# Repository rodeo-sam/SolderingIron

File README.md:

SolderingIron
=============

Idea for an OpenSource Soldering Iron

This project is just another avr based soldering iron. Since professional equipment is quite pricy and not very complicated this projects takes a good, changeable soldering iron tip like the Weller RT1 and provides all the electronics behind that.

## Features
* open hardware (schematic and layout made in Eagle 7.2 freeware license)
* open firmware written in C (not ready to use right now)
* fast heatup
* saving and restoring temperature to and from EEPROM
* high-precision op-amp for temperature measurement
* safety measures against overheating and controller crashes
* automatic temperature control (pid controller)
* different temperature scales available (recompiling necessary)
* solder tip rest detection via hall sensor (optional)
* almost all parts are available from the [Seeedstudio Open Parts Library](http://www.seeedstudio.com/wiki/Open_parts_library)

## How does it work
* 5V for logic
* 12V for soldering iron
* ATmega328p controlled

### Temperature measure
The thermo-voltage signal is amplified by an op-amp with a gain
	`g = 1 + R1/R2 = 1 + 51k/100 = 511`
this signal is converted by ADC0 using Vcc=5V as voltage reference

### Solder tip detection
Solved by a hall sensor connected to ADC2. This sensor is powered by 5V

## References
### Links:
* [arduino uno shield](http://www.martin-kumm.de/wiki/doku.php?id=Projects:SMD_Solderstation)
  * Forum discussion + group order coordination [Thema: DIY SMD - Lötstation Ersatz für (WELLER)](http://fpv-community.de/showthread.php?41335-DIY-SMD-Lötstation-Ersatz-für-(WELLER))
* [original Weller cable](http://www.pewa.de/cgi-bin/cosmoshop/lshop.cgi?action=showdetail&wkid=1415179514-14110&ls=d&nc=1415179711-29852&rubnum=&artnum=C-51042699&file=&gesamt_zeilen=0Tsuche--silikon)
* unfinished project [Custom Weller WSM 1 style controller for RT series tips](http://dangerousprototypes.com/forum/viewtopic.php?f=19&t=3583)
* [Thermoelement im Weller WMRP.](http://www.mikrocontroller.net/topic/175412#1686071)

### Datasheets:
* power MOSFET [IRF7424](http://www.irf.com/product-info/datasheets/data/irf7424.pdf)
* Voltage regulator [REG1117](http://www.ti.com/lit/pdf/SBVS001)
* uC [ATmega328P](http://www.atmel.com/devices/atmega328p.aspx)
* Quad OP-Amp [LM324D](http://pdf1.alldatasheet.com/datasheet-pdf/view/22759/STMICROELECTRONICS/LM324D.html)
* Single OP-Amp [OPA336u](http://www.ti.com/lit/ds/symlink/opa336.pdf)
* Solder Tip [Weller RT1](http://datasheet.octopart.com/RT1-Cooper-Tools-datasheet-13539183.pdf)
* Solder Tip detector [Hallsensor unipolar](http://www.reichelt.de/index.html?&ACTION=7&LA=3&OPEN=0&INDEX=0&FILENAME=B400%252FTLE4905L_TLE4935L_TLE4945L_TLE4935-2L%2523SIE.pdf)

### Current State:
* hardware version 1.2 is almost ready to be produced
* optimized bill of materials by reducing unnecessary components
* PCB measures 5cm x 5cm
* individual 7-segment displays in use (broader availability)
* I2C is now unused and can be used for additional hardware

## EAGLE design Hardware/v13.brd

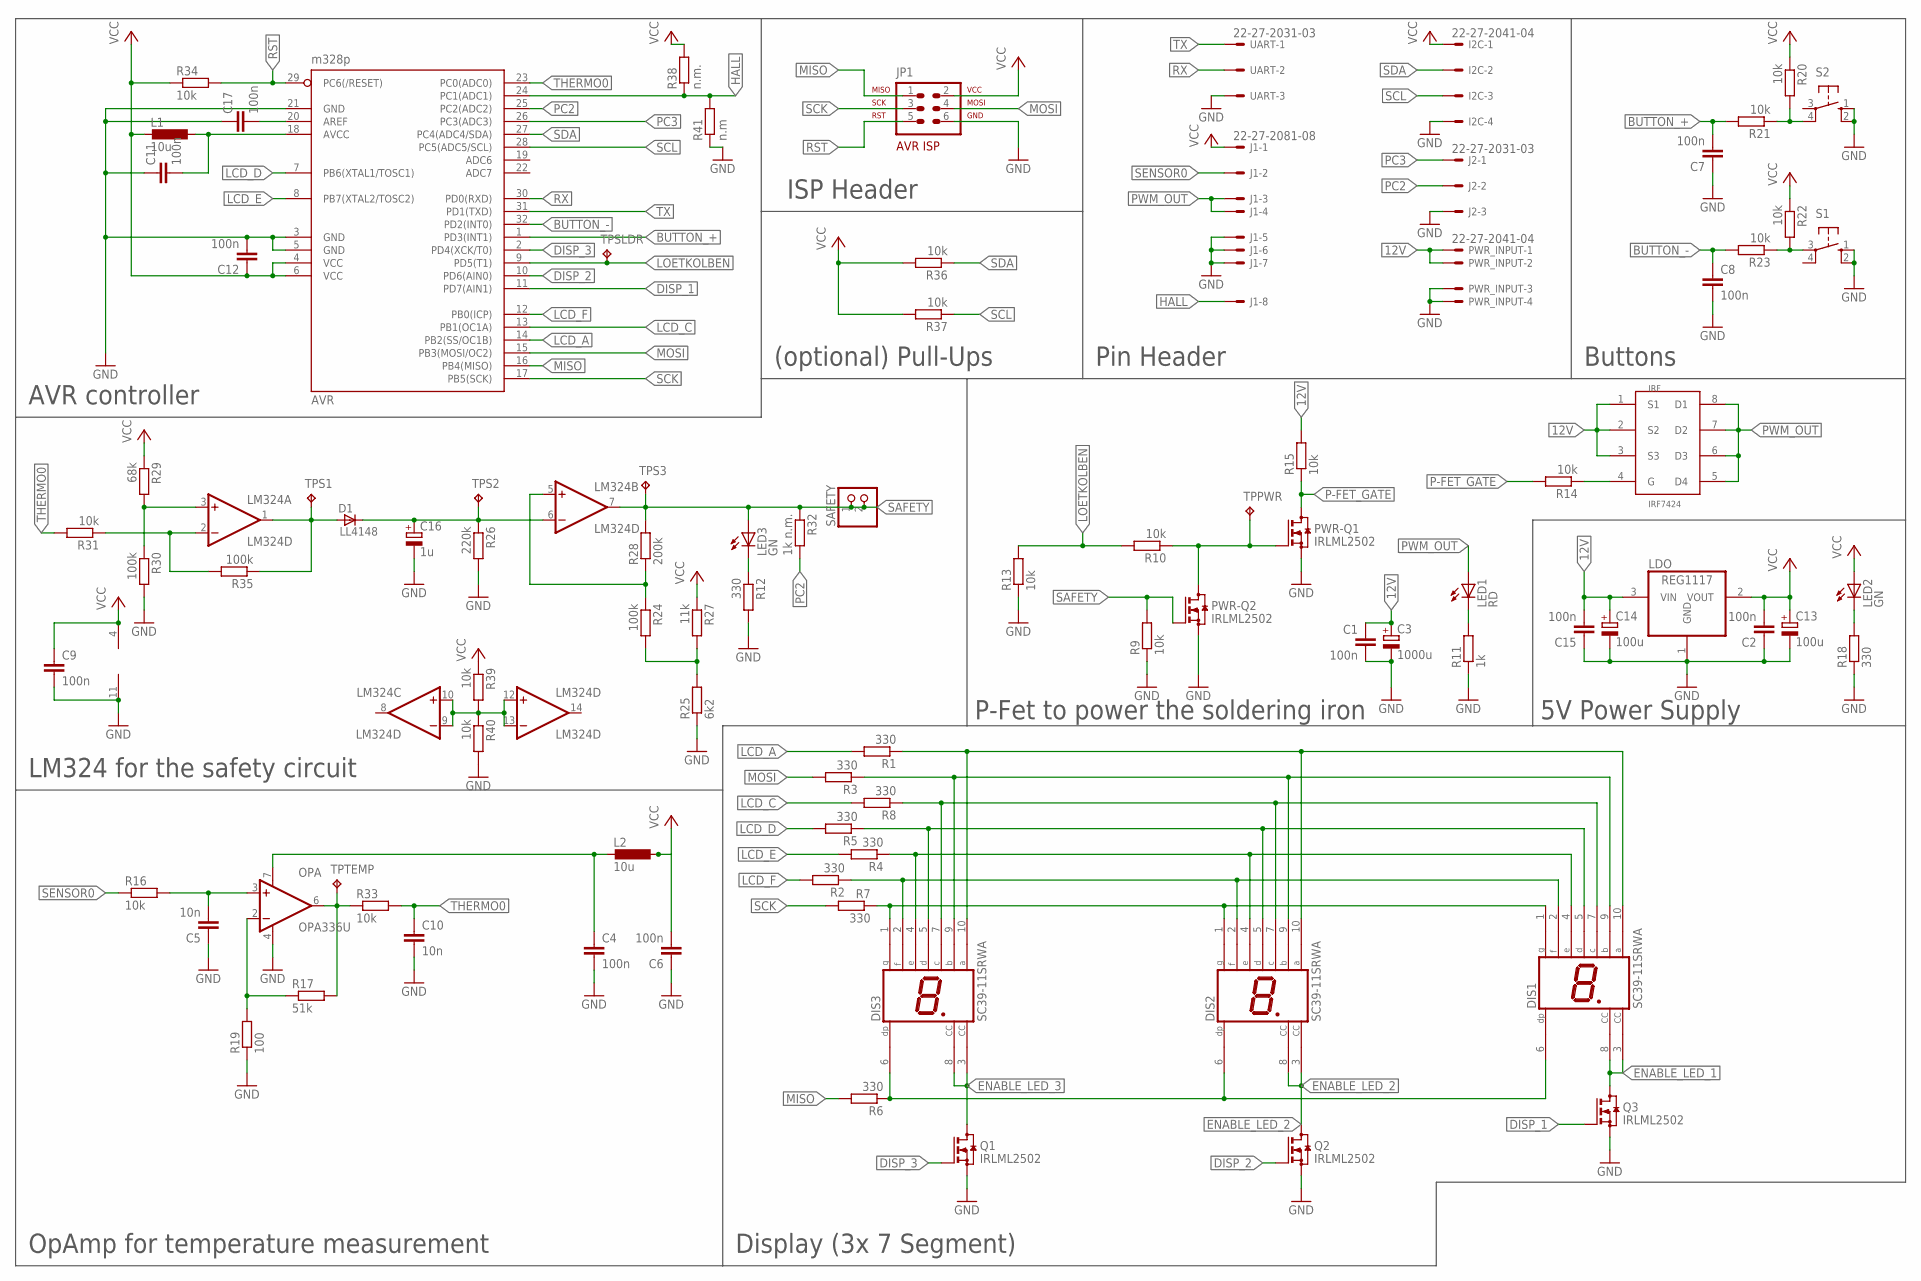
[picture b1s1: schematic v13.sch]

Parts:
AVR: m328p; TQFP32-08
C1, C2, C4, C6, C7, C8, C9, C11, C12, C15, C17: 100n; C0603
C3: 1000u; E5-13
C5, C10: 10n; C0603
C13, C14: 100u; E2-5
C16: 1u; E2-5
D1: LL4148; SOD80_DO213AA_MINIMELF
DIS1, DIS2, DIS3: SC39-11SRWA; HDSP-E
I2C: 22-27-2041-04; 6410-04
IRF: IRF7424; SO-08
J1: 22-27-2081-08; 6410-08
J2: 22-27-2031-03; 6410-03
JP1: AVR-ISP-6VERT; AVR-ISP-6
L1, L2: 10u; L2825P
LDO: REG1117; SOT223
LED1: RD; CHIP-LED0805
LED2, LED3: GN; CHIP-LED0805
LM324: LM324D; SO14
OPA: OPA336U; SO08
PWR-Q1, PWR-Q2: IRLML2502; SOT23
PWR_INPUT: 22-27-2041-04; 6410-04
Q1, Q2, Q3: IRLML2502; SOT23
R1, R2, R3, R4, R5, R6, R7, R8, R12, R18: 330; R0603
R9, R10, R13, R14, R15, R16, R20, R21, R22, R23, R31, R33, R34, R36, R37, R39, R40: 10k; R0603
R11: 1k; R0603
R17: 51k; R0603
R19: 100; R0603
R24, R30, R35: 100k; R0603
R25: 6k2; R0603
R26: 220k; R0603
R27: 11k; R0603
R28: 200k; R0603
R29: 68k; R0603
R32: 1k n.m.; R0603
R38: n.m.; R0603
R41: n.m; R0603
S1, S2: 10-XX; B3F-10XX
SAFETY: PINHD-1X2; 1X02
TPPWR: TPB1,27; B1,27
TPS1, TPS2, TPS3: TPB1,27; B1,27
TPSLDR: TPB1,27; B1,27
TPTEMP: TPB1,27; B1,27
UART: 22-27-2031-03; 6410-03

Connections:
12V: C1.1, C3.+, C14.+, C15.2, IRF.1 (S1), IRF.2 (S2), IRF.3 (S3), LDO.3 (VIN), PWR_INPUT.1, PWR_INPUT.2, R15.2
AREF: AVR.20 (AREF), C17.2
AVCC: AVR.18 (AVCC), C11.2, L1.1
BUTTON_+: AVR.1 (PD3(INT1)), C7.2, R21.2
BUTTON_-: AVR.32 (PD2(INT0)), C8.1, R23.2
DISP_1: AVR.11 (PD7(AIN1)), Q3.1 (G)
DISP_2: AVR.10 (PD6(AIN0)), Q2.1 (G)
DISP_3: AVR.2 (PD4(XCK/T0)), Q1.1 (G)
ENABLE_LED_1: DIS1.3 (CC), DIS1.8 (CC), Q3.3 (D)
ENABLE_LED_2: DIS2.3 (CC), DIS2.8 (CC), Q2.3 (D)
ENABLE_LED_3: DIS3.3 (CC), DIS3.8 (CC), Q1.3 (D)
GND: AVR.3 (GND), AVR.5 (GND), AVR.21 (GND), C1.2, C2.1, C3.-, C4.2, C5.1, C6.1, C7.1, C8.2, C9.2, C10.2, C11.1, C12.2, C13.-, C14.-, C15.1, C16.-, C17.1, I2C.4, J1.5, J1.6, J1.7, J2.3, JP1.6, LDO.1 (GND), LM324.11 (V-), OPA.4 (V-), PWR-Q1.2 (S), PWR-Q2.2 (S), PWR_INPUT.3, PWR_INPUT.4, Q1.2 (S), Q2.2 (S), Q3.2 (S), R9.1, R11.1, R12.2, R13.1, R18.1, R19.1, R25.1, R26.2, R30.2, R40.2, R41.1, S1.1 (S), S1.2 (S1), S2.1 (S), S2.2 (S1), UART.3
HALL: AVR.24 (PC1(ADC1)), J1.8, R38.1, R41.2
LCD_A: AVR.14 (PB2(SS/OC1B)), R1.2
LCD_C: AVR.13 (PB1(OC1A)), R8.2
LCD_D: AVR.7 (PB6(XTAL1/TOSC1)), R5.2
LCD_E: AVR.8 (PB7(XTAL2/TOSC2)), R4.2
LCD_F: AVR.12 (PB0(ICP)), R2.2
LOETKOLBEN: AVR.9 (PD5(T1)), R10.2, R13.2, TPSLDR.TP
MISO: AVR.16 (PB4(MISO)), JP1.1, R6.2
MOSI: AVR.15 (PB3(MOSI/OC2)), JP1.4, R3.2
unnamed: OPA.2 (-IN), R17.1, R19.2
unnamed: LED3.C, R12.1
unnamed: LM324.2 (-IN), R31.1, R35.2
unnamed: LM324.9 (-IN), LM324.10 (+IN), LM324.12 (+IN), LM324.13 (-IN), R39.2, R40.1
unnamed: C4.1, L2.2, OPA.7 (V+)
unnamed: D1.A, LM324.1 (OUT), R35.1, TPS1.TP
unnamed: LM324.3 (+IN), R29.2, R30.1
unnamed: C16.+, D1.C, LM324.6 (-IN), R26.1, TPS2.TP
unnamed: LM324.5 (+IN), R24.1, R28.1
unnamed: R24.2, R25.2, R27.2
unnamed: IRF.4 (G), R14.1
unnamed: PWR-Q1.1 (G), PWR-Q2.3 (D), R10.1, TPPWR.TP
unnamed: R22.2, R23.1, S1.3
unnamed: R20.2, R21.1, S2.4 (P1)
unnamed: LED2.C, R18.2
unnamed: LED1.C, R11.2
unnamed: C5.2, OPA.3 (+IN), R16.2
unnamed: DIS1.6 (DP), DIS2.6 (DP), DIS3.6 (DP), R6.1
unnamed: DIS1.2 (F), DIS2.2 (F), DIS3.2 (F), R2.1
unnamed: DIS1.1 (G), DIS2.1 (G), DIS3.1 (G), R7.1
unnamed: DIS1.4 (E), DIS2.4 (E), DIS3.4 (E), R4.1
unnamed: DIS1.5 (D), DIS2.5 (D), DIS3.5 (D), R5.1
unnamed: DIS1.7 (C), DIS2.7 (C), DIS3.7 (C), R8.1
unnamed: DIS1.9 (B), DIS2.9 (B), DIS3.9 (B), R3.1
unnamed: DIS1.10 (A), DIS2.10 (A), DIS3.10 (A), R1.1
OPA_OUT: OPA.6 (OUT), R17.2, R33.1, TPTEMP.TP
P-FET_GATE: PWR-Q1.3 (D), R14.2, R15.1
PC2: AVR.25 (PC2(ADC2)), J2.2, R32.2
PC3: AVR.26 (PC3(ADC3)), J2.1
PWM_OUT: IRF.5 (D4), IRF.6 (D3), IRF.7 (D2), IRF.8 (D1), J1.3, J1.4, LED1.A
RST: AVR.29 (PC6(/RESET)), JP1.5, R34.2
RX: AVR.30 (PD0(RXD)), UART.2
SAFETY: LED3.A, LM324.7 (OUT), PWR-Q2.1 (G), R9.2, R28.2, R32.1, SAFETY.1, SAFETY.2, TPS3.TP
SCK: AVR.17 (PB5(SCK)), JP1.3, R7.2
SCL: AVR.28 (PC5(ADC5/SCL)), I2C.3, R37.1
SDA: AVR.27 (PC4(ADC4/SDA)), I2C.2, R36.1
SENSOR0: J1.2, R16.1
THERMO0: AVR.23 (PC0(ADC0)), C10.1, R31.2, R33.2
TX: AVR.31 (PD1(TXD)), UART.1
VCC: AVR.4 (VCC), AVR.6 (VCC), C2.2, C6.2, C9.1, C12.1, C13.+, I2C.1, J1.1, JP1.2, L1.2, L2.1, LDO.2 (VOUT), LED2.A, LM324.4 (V+), R20.1, R22.1, R27.1, R29.1, R34.1, R36.2, R37.2, R38.2, R39.1

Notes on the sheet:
Buttons
AVR controller
P-Fet to power the soldering iron
5V Power Supply
ISP Header
OpAmp for temperature measurement
Display (3x 7 Segment)
Pin Header
LM324 for the safety circuit
(optional) Pull-Ups

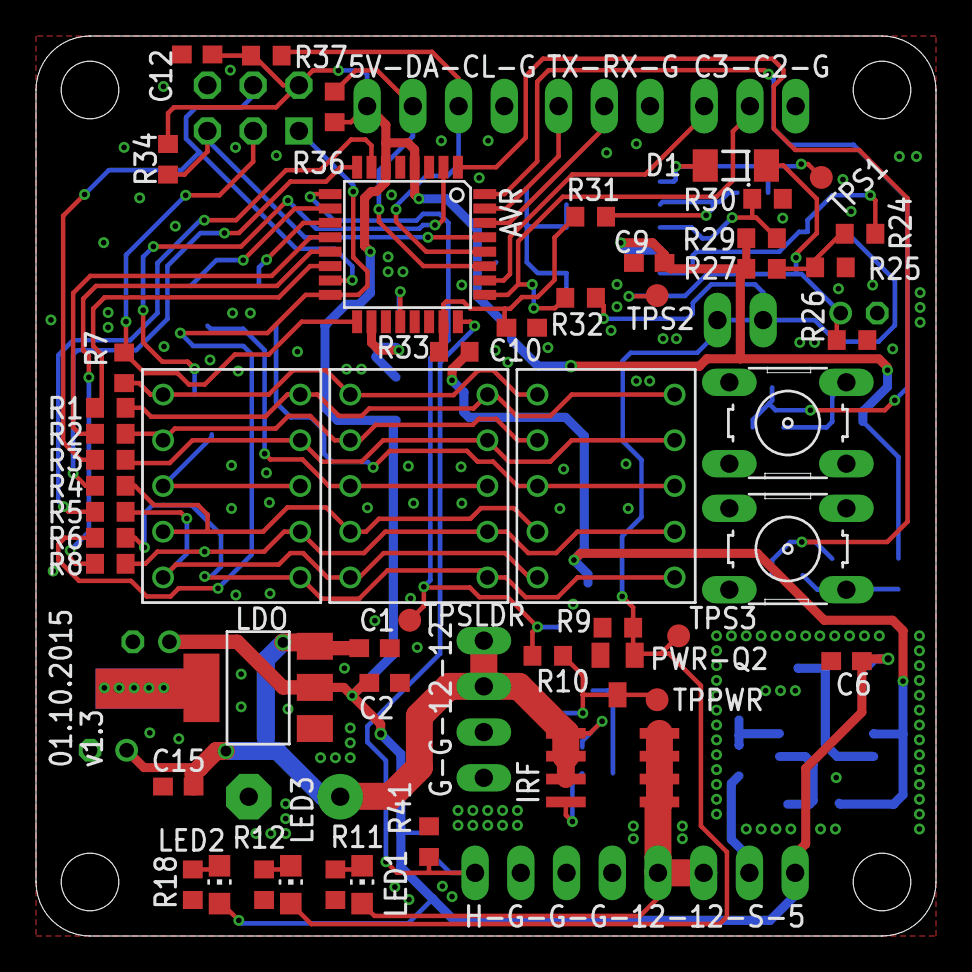
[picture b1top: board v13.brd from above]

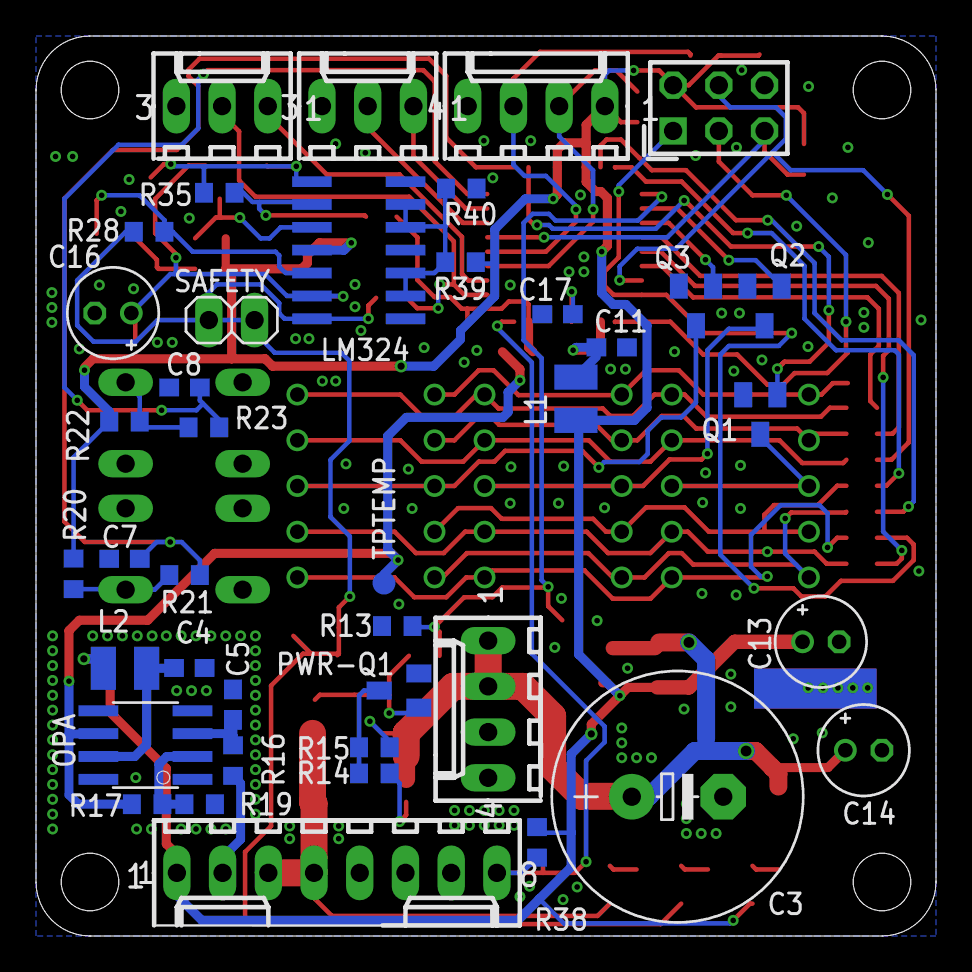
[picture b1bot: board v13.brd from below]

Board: 4 copper layers, 50.0 x 50.0 mm, 92 parts (41 on the bottom side), 61 nets.

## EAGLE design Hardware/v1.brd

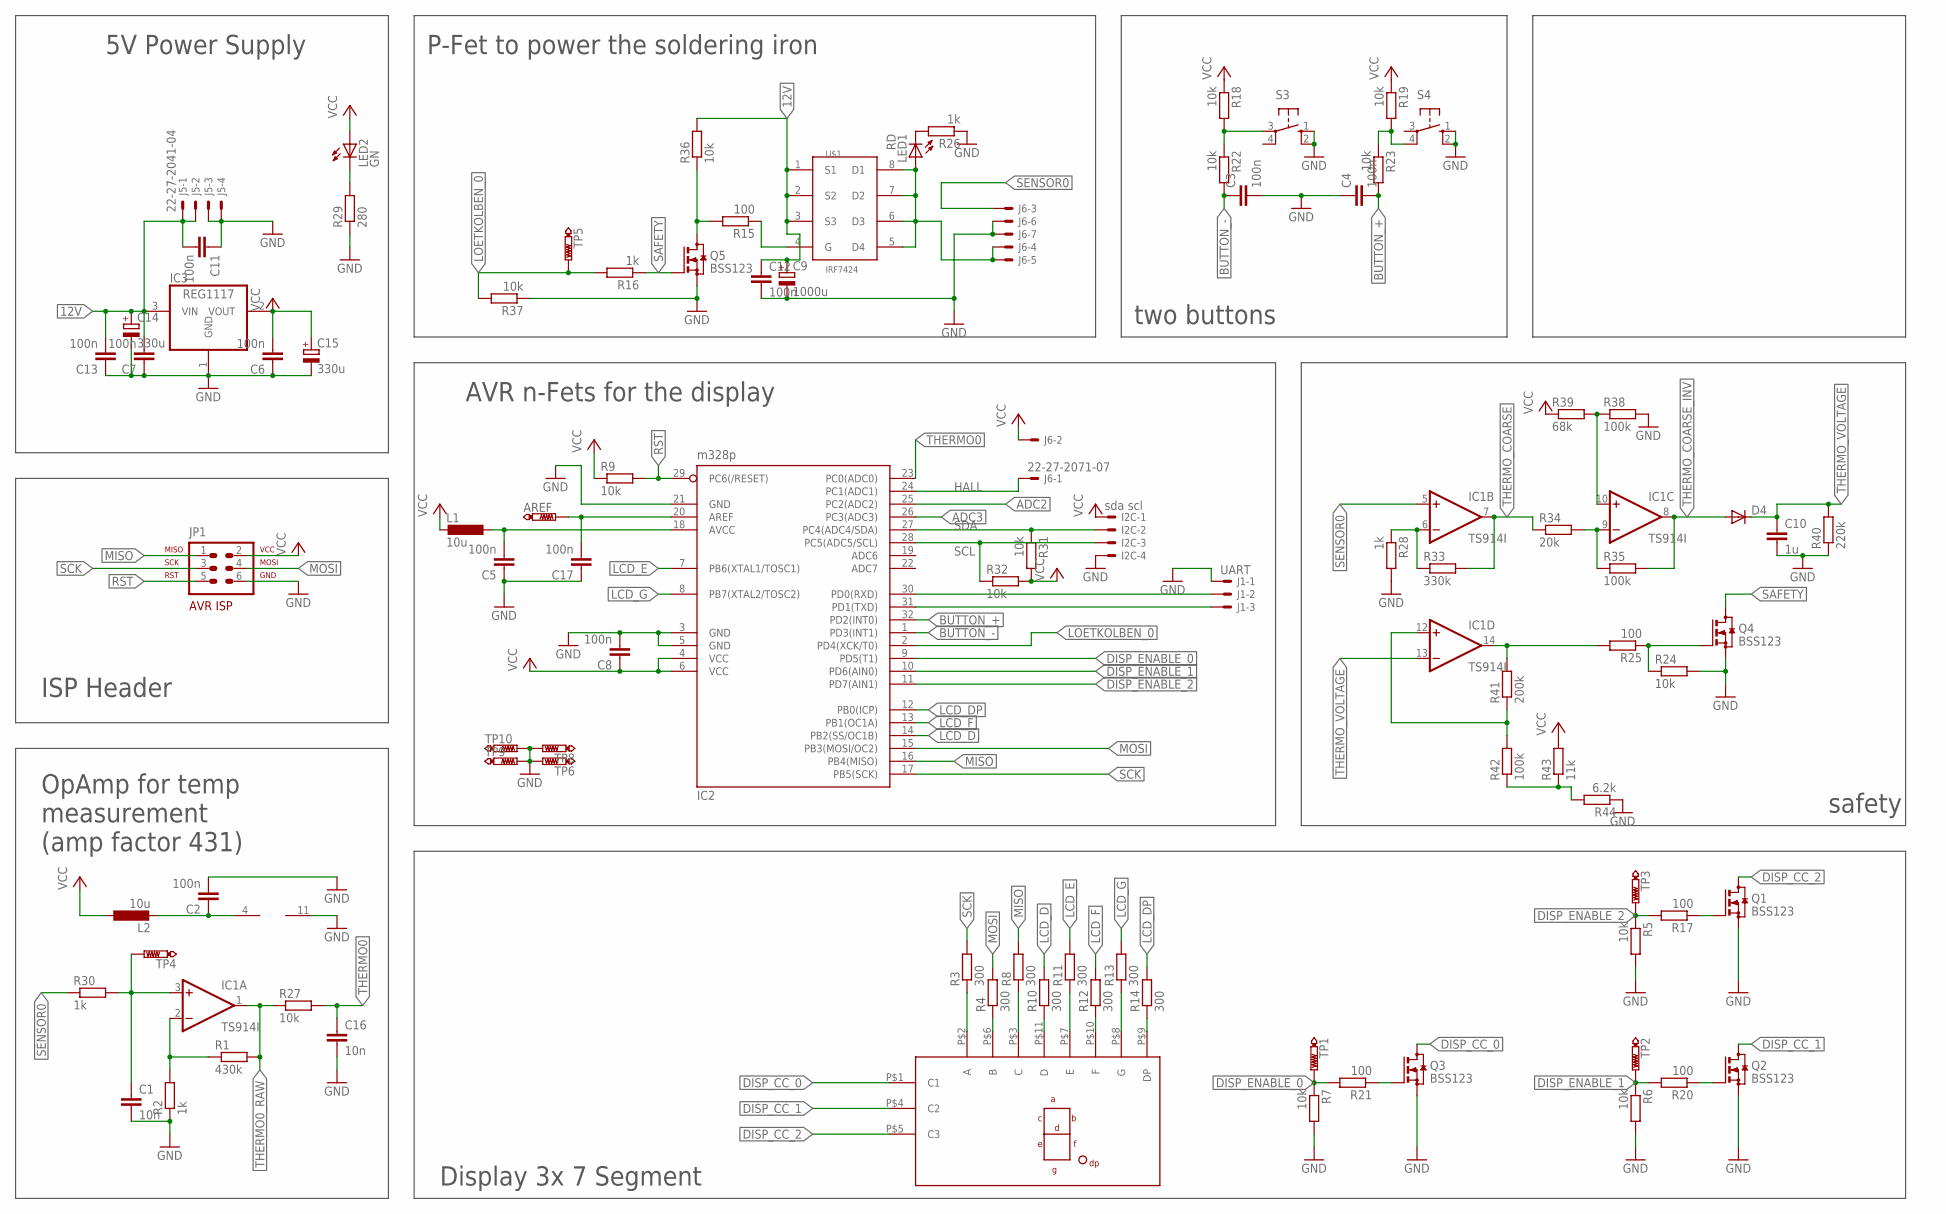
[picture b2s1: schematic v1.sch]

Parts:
AREF: PTR1B1,27; B1,27
C1, C16: 10n; C0603
C2, C3, C4, C5, C6, C7, C8, C11, C12, C13, C17: 100n; C0603
C9: 1000u; E5-13
C10: 1u; C0805
C14: 330u; E3,5-8
C15: 330u; E2-5
D4: DIODE-DO214AC; DO214AC
I2C: sda scl; 6410-04
IC1: TS914I; SO14
IC2: m328p; TQFP32-08
IC3: REG1117; SOT223
J1: UART; 6410-03
J5: 22-27-2041-04; 6410-04
J6: 22-27-2071-07; 6410-07
JP1: AVR-ISP-6VERT; AVR-ISP-6
L1, L2: 10u; L2825P
LED1: RD; CHIP-LED0805
LED2: GN; CHIP-LED0805
Q1, Q2, Q3, Q4, Q5: BSS123; SOT23
R1: 430k; R0603
R2, R16, R26, R28, R30: 1k; R0603
R3, R4, R8, R10, R11, R12, R13, R14: 300; R0603
R5, R6, R7, R9, R18, R19, R22, R23, R24, R27, R31, R32, R36, R37: 10k; R0603
R15, R17, R20, R21, R25: 100; R0603
R29: 280; R0603
R33: 330k; R0603
R34: 20k; R0603
R35, R38, R42: 100k; R0603
R39: 68k; R0603
R40: 220k; R0603
R41: 200k; R0603
R43: 11k; R0603
R44: 6.2k; R0603
S3, S4: 10-XX; B3F-10XX
TP1, TP2, TP3, TP4, TP5, TP6, TP8, TP9, TP10: PTR1B1,27; B1,27
U$1: IRF7424; SO-08
U$2: 3X7SEG

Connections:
12V: C7.2, C9.+, C11.2, C12.1, C13.2, C14.+, IC3.3 (VIN), J5.1, J5.2, R36.2, U$1.1 (S1), U$1.2 (S2), U$1.3 (S3)
ADC2: IC2.25 (PC2(ADC2))
ADC3: IC2.26 (PC3(ADC3))
AREF: AREF.TP, C17.2, IC2.20 (AREF)
BUTTON_+: C4.2, IC2.32 (PD2(INT0)), R23.2
BUTTON_-: C3.1, IC2.1 (PD3(INT1)), R22.2
DISP_CC_0: Q3.3 (D), U$2.P$1 (C1)
DISP_CC_1: Q2.3 (D), U$2.P$4 (C2)
DISP_CC_2: Q1.3 (D), U$2.P$5 (C3)
DISP_ENABLE_0: IC2.9 (PD5(T1)), R7.1, R21.2, TP1.TP
DISP_ENABLE_1: IC2.10 (PD6(AIN0)), R6.1, R20.2, TP2.TP
DISP_ENABLE_2: IC2.11 (PD7(AIN1)), R5.1, R17.2, TP3.TP
GND: C1.2, C2.2, C3.2, C4.1, C5.1, C6.1, C7.1, C8.2, C9.-, C10.2, C11.1, C12.2, C13.1, C14.-, C15.-, C16.2, C17.1, I2C.4, IC1.11 (V-), IC2.3 (GND), IC2.5 (GND), IC2.21 (GND), IC3.1 (GND), J1.1, J5.3, J5.4, J6.6, J6.7, JP1.6, Q1.2 (S), Q2.2 (S), Q3.2 (S), Q4.2 (S), Q5.2 (S), R2.1, R5.2, R6.2, R7.2, R24.2, R26.1, R28.2, R29.1, R37.1, R38.2, R40.1, R44.1, S3.1 (S), S3.2 (S1), S4.1 (S), S4.2 (S1), TP6.TP, TP8.TP, TP9.TP, TP10.TP
HALL: IC2.24 (PC1(ADC1)), J6.1
LCD_D: IC2.14 (PB2(SS/OC1B)), R10.2
LCD_DP: IC2.12 (PB0(ICP)), R14.2
LCD_E: IC2.7 (PB6(XTAL1/TOSC1)), R11.2
LCD_F: IC2.13 (PB1(OC1A)), R12.2
LCD_G: IC2.8 (PB7(XTAL2/TOSC2)), R13.2
LOETKOLBEN_0: IC2.2 (PD4(XCK/T0)), R16.2, R37.2, TP5.TP
MISO: IC2.16 (PB4(MISO)), JP1.1, R8.2
MOSI: IC2.15 (PB3(MOSI/OC2)), JP1.4, R4.2
unnamed: IC1.2 (-IN), R1.1, R2.2
unnamed: IC2.31 (PD1(TXD)), J1.3
unnamed: C5.2, IC2.18 (AVCC), L1.1
unnamed: IC2.30 (PD0(RXD)), J1.2
unnamed: C2.1, IC1.4 (V+), L2.2
unnamed: R3.1, U$2.P$2 (A)
unnamed: R4.1, U$2.P$6 (B)
unnamed: R8.1, U$2.P$3 (C)
unnamed: R10.1, U$2.P$11 (D)
unnamed: Q4.1 (G), R24.1, R25.1
unnamed: R11.1, U$2.P$7 (E)
unnamed: R12.1, U$2.P$10 (F)
unnamed: R13.1, U$2.P$8 (G)
unnamed: R14.1, U$2.P$9 (DP)
unnamed: R15.1, U$1.4 (G)
unnamed: IC1.6 (-IN), R28.1, R33.1
unnamed: Q2.1 (G), R20.1
unnamed: Q1.1 (G), R17.1
unnamed: Q3.1 (G), R21.1
unnamed: IC1.9 (-IN), R34.2, R35.1
unnamed: IC1.12 (+IN), R41.1, R42.2
unnamed: R18.2, R22.1, S3.3
unnamed: R19.2, R23.1, S4.4 (P1)
unnamed: LED2.C, R29.2
unnamed: LED1.C, R26.2
unnamed: IC1.10 (+IN), R38.1, R39.2
unnamed: C1.1, IC1.3 (+IN), R30.2, TP4.TP
unnamed: R42.1, R43.1, R44.2
unnamed: IC1.14 (OUT), R25.2, R41.2
unnamed: Q5.3 (D), R15.2, R36.1
unnamed: J6.4, J6.5, LED1.A, U$1.5 (D4), U$1.6 (D3), U$1.7 (D2), U$1.8 (D1)
RST: IC2.29 (PC6(/RESET)), JP1.5, R9.2
SAFETY: Q4.3 (D), Q5.1 (G), R16.1
SCK: IC2.17 (PB5(SCK)), JP1.3, R3.2
SCL: I2C.3, IC2.28 (PC5(ADC5/SCL)), R32.1
SDA: I2C.2, IC2.27 (PC4(ADC4/SDA)), R31.1
SENSOR0: IC1.5 (+IN), J6.3, R30.1
THERMO0: C16.1, IC2.23 (PC0(ADC0)), R27.2
THERMO0_RAW: IC1.1 (OUT), R1.2, R27.1
THERMO_COARSE: IC1.7 (OUT), R33.2, R34.1
THERMO_COARSE_INV: D4.A, IC1.8 (OUT), R35.2
THERMO_VOLTAGE: C10.1, D4.C, IC1.13 (-IN), R40.2
VCC: C6.2, C8.1, C15.+, I2C.1, IC2.4 (VCC), IC2.6 (VCC), IC3.2 (VOUT), J6.2, JP1.2, L1.2, L2.1, LED2.A, R9.1, R18.1, R19.1, R31.2, R32.2, R39.1, R43.2

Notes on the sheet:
two buttons
AVR n-Fets for the display
P-Fet to power the soldering iron
5V Power Supply
ISP Header
OpAmp for temp measurement (amp factor 431)
Display 3x 7 Segment
safety

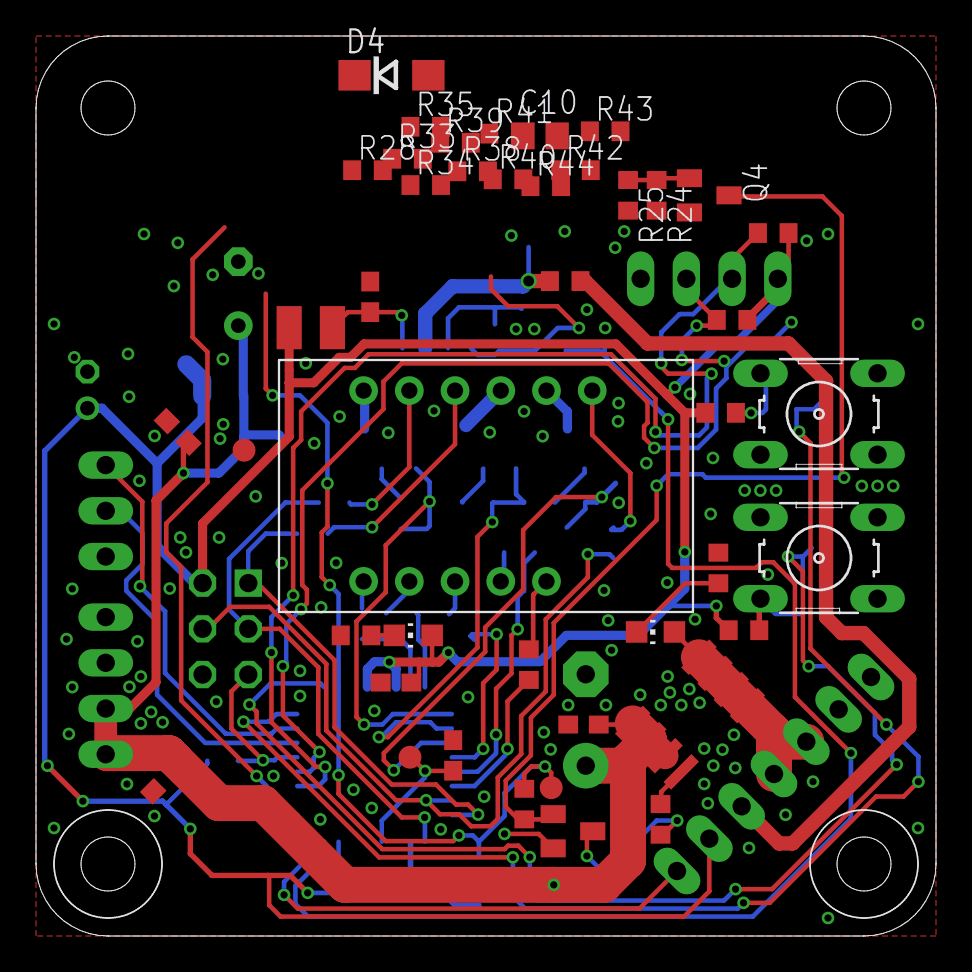
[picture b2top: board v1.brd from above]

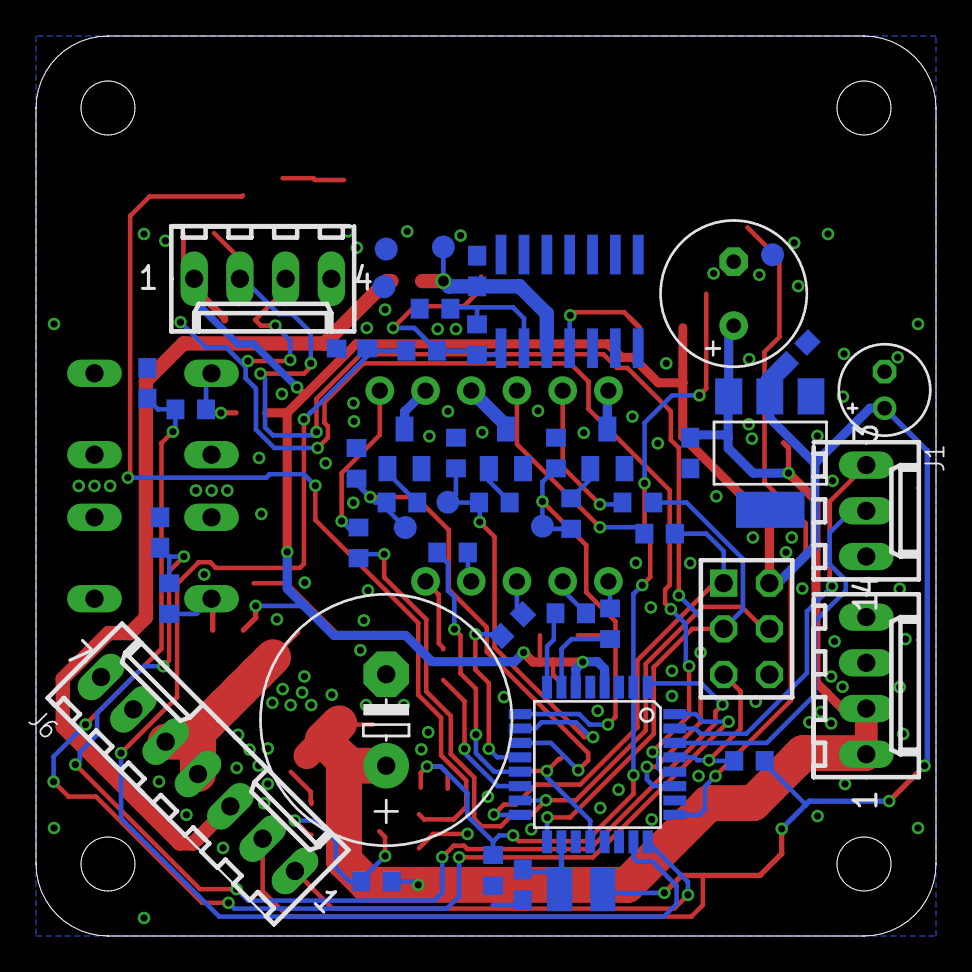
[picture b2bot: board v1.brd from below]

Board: 2 copper layers, 50.0 x 50.0 mm, 93 parts (50 on the bottom side), 63 nets.

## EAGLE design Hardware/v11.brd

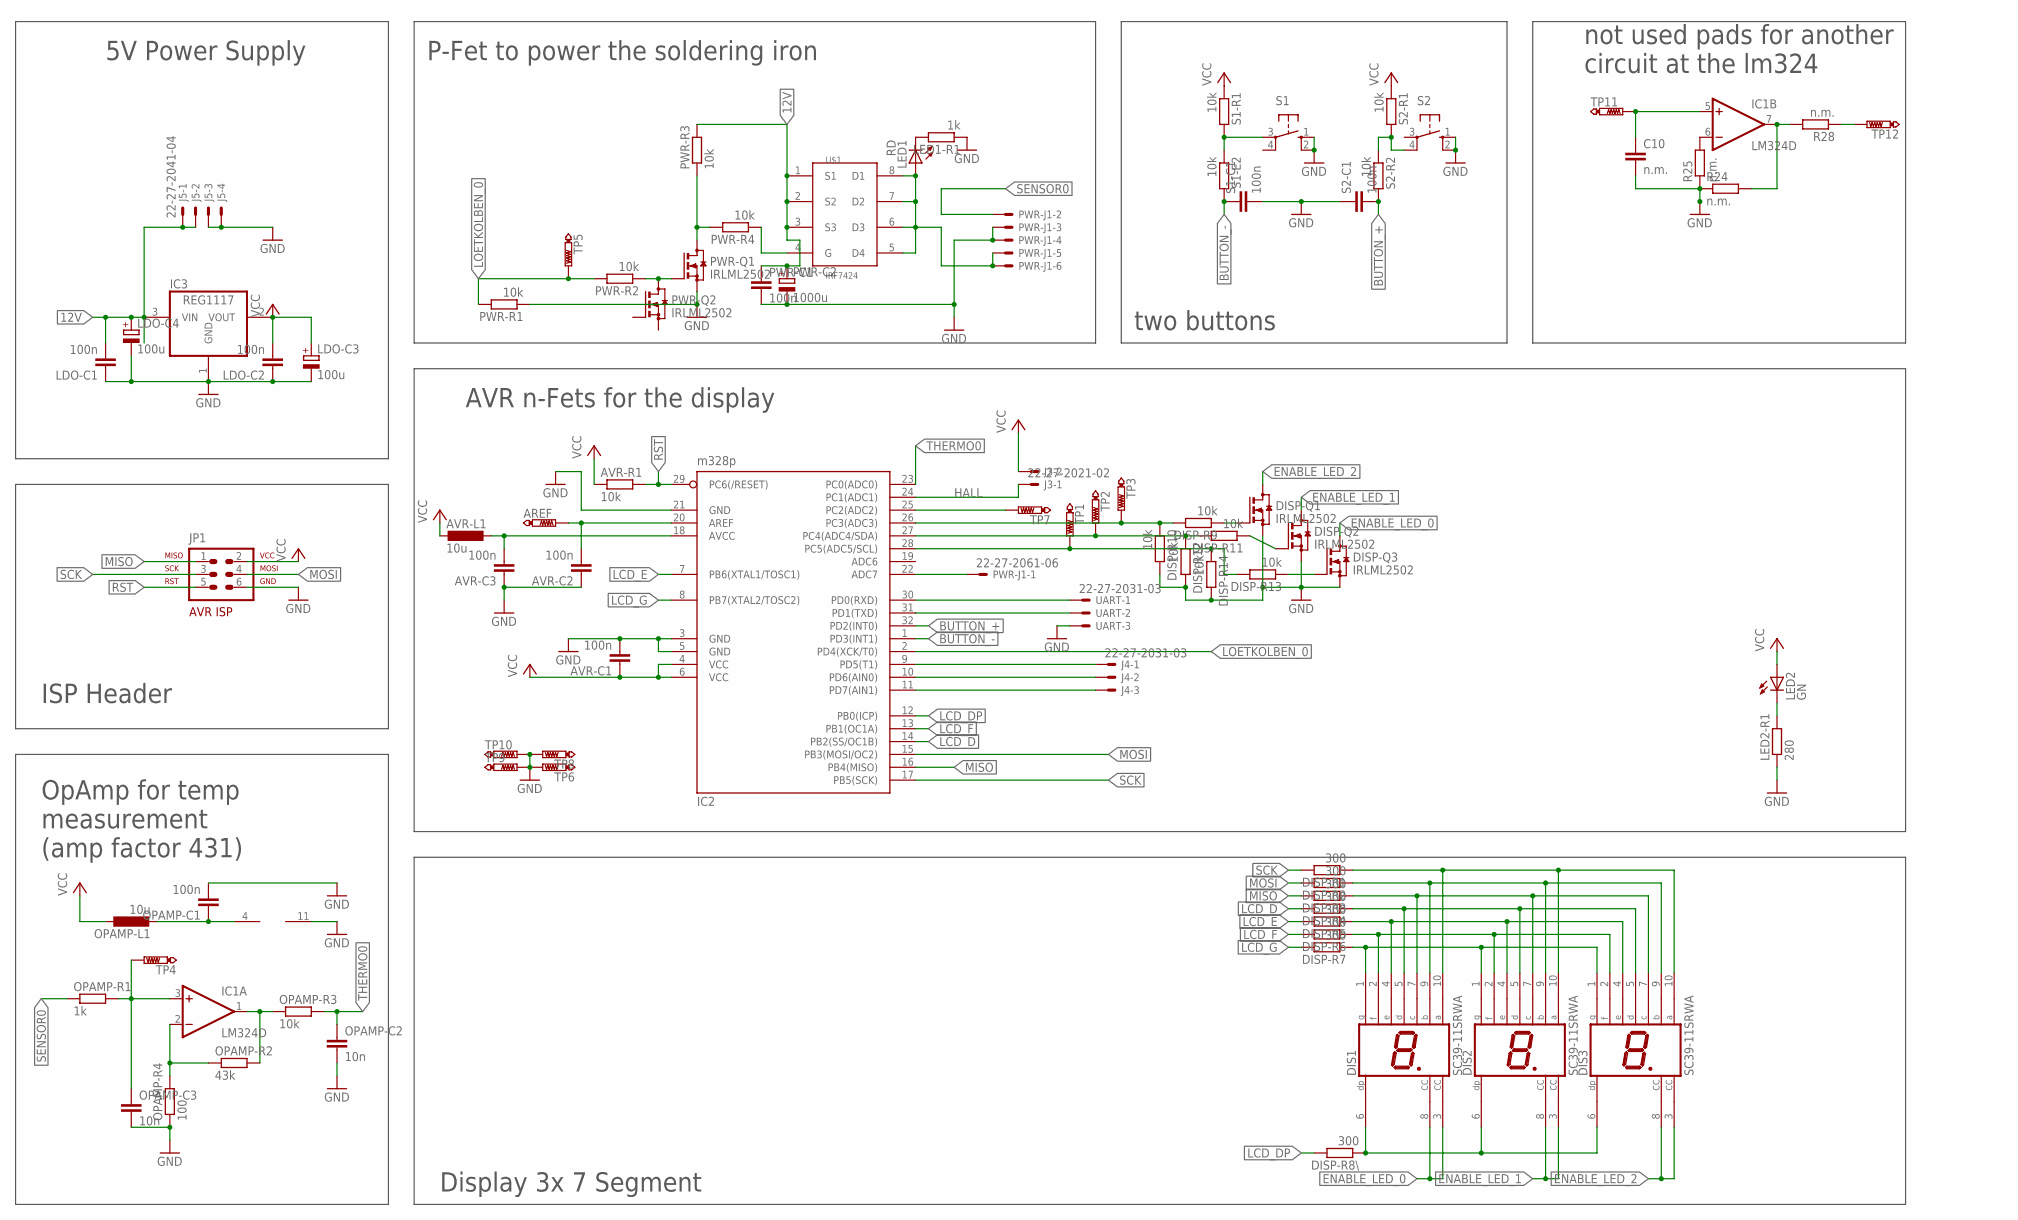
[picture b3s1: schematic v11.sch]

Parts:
AREF: PTR1B1,27; B1,27
AVR-C1, AVR-C2, AVR-C3: 100n; C0603
AVR-L1: 10u; L2825P
AVR-R1: 10k; R0603
C10: n.m.; C0603
DIS1, DIS2, DIS3: SC39-11SRWA; HDSP-E
DISP-Q1, DISP-Q2, DISP-Q3: IRLML2502; SOT23
DISP-R1, DISP-R2, DISP-R3, DISP-R4, DISP-R5, DISP-R6, DISP-R7, DISP-R8\: 300; R0603
DISP-R9, DISP-R10, DISP-R11, DISP-R12, DISP-R13, DISP-R14: 10k; R0603
IC1: LM324D; SO14
IC2: m328p; TQFP32-08
IC3: REG1117; SOT223
J3: 22-27-2021-02; 6410-02
J4: 22-27-2031-03; 6410-03
J5: 22-27-2041-04; 6410-04
JP1: AVR-ISP-6VERT; AVR-ISP-6
LDO-C1, LDO-C2: 100n; C0603
LDO-C3, LDO-C4: 100u; E2-5
LED1: RD; CHIP-LED0805
LED1-R1: 1k; R0603
LED2: GN; CHIP-LED0805
LED2-R1: 280; R0603
OPAMP-C1: 100n; C0603
OPAMP-C2, OPAMP-C3: 10n; C0603
OPAMP-L1: 10u; L2825P
OPAMP-R1: 1k; R0603
OPAMP-R2: 43k; R0603
OPAMP-R3: 10k; R0603
OPAMP-R4: 100; R0603
PWR-C1: 100n; C0603
PWR-C2: 1000u; E5-13
PWR-J1: 22-27-2061-06; 6410-06
PWR-Q1, PWR-Q2: IRLML2502; SOT23
PWR-R1, PWR-R2, PWR-R3, PWR-R4: 10k; R0603
R24, R25, R28: n.m.; R0603
S1, S2: 10-XX; B3F-10XX
S1-C1, S2-C1: 100n; C0603
S1-E2, S1-R1, S2-R1, S2-R2: 10k; R0603
TP1, TP2, TP3, TP4, TP5, TP6, TP7, TP8, TP9, TP10, TP11, TP12: PTR1B1,27; B1,27
U$1: IRF7424; SO-08
UART: 22-27-2031-03; 6410-03

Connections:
12V: IC3.3 (VIN), J5.1, J5.2, LDO-C1.2, LDO-C4.+, PWR-C1.1, PWR-C2.+, PWR-R3.2, U$1.1 (S1), U$1.2 (S2), U$1.3 (S3)
ADC2: IC2.25 (PC2(ADC2)), TP7.TP
ADC7: IC2.22 (ADC7), PWR-J1.1
AREF: AREF.TP, AVR-C2.2, IC2.20 (AREF)
BUTTON_+: IC2.32 (PD2(INT0)), S2-C1.2, S2-R2.2
BUTTON_-: IC2.1 (PD3(INT1)), S1-C1.1, S1-E2.2
ENABLE_LED_0: DIS1.3 (CC), DIS1.8 (CC), DISP-Q3.3 (D)
ENABLE_LED_1: DIS2.3 (CC), DIS2.8 (CC), DISP-Q2.3 (D)
ENABLE_LED_2: DIS3.3 (CC), DIS3.8 (CC), DISP-Q1.3 (D)
GND: AVR-C1.2, AVR-C2.1, AVR-C3.1, C10.2, DISP-Q1.2 (S), DISP-Q2.2 (S), DISP-Q3.2 (S), DISP-R10.2, DISP-R12.2, DISP-R14.2, IC1.11 (V-), IC2.3 (GND), IC2.5 (GND), IC2.21 (GND), IC3.1 (GND), J5.3, J5.4, JP1.6, LDO-C1.1, LDO-C2.1, LDO-C3.-, LDO-C4.-, LED1-R1.1, LED2-R1.1, OPAMP-C1.2, OPAMP-C2.2, OPAMP-C3.2, OPAMP-R4.1, PWR-C1.2, PWR-C2.-, PWR-J1.3, PWR-J1.4, PWR-Q1.2 (S), PWR-R1.1, R24.1, R25.1, S1.1 (S), S1.2 (S1), S1-C1.2, S2.1 (S), S2.2 (S1), S2-C1.1, TP6.TP, TP8.TP, TP9.TP, TP10.TP, UART.3
HALL: IC2.24 (PC1(ADC1)), J3.1
LCD_D: DISP-R4.2, IC2.14 (PB2(SS/OC1B))
LCD_DP: DISP-R8\.2, IC2.12 (PB0(ICP))
LCD_E: DISP-R5.2, IC2.7 (PB6(XTAL1/TOSC1))
LCD_F: DISP-R6.2, IC2.13 (PB1(OC1A))
LCD_G: DISP-R7.2, IC2.8 (PB7(XTAL2/TOSC2))
LOETKOLBEN_0: IC2.2 (PD4(XCK/T0)), PWR-R1.2, PWR-R2.2, TP5.TP
MISO: DISP-R3.2, IC2.16 (PB4(MISO)), JP1.1
MOSI: DISP-R2.2, IC2.15 (PB3(MOSI/OC2)), JP1.4
unnamed: IC1.2 (-IN), OPAMP-R2.1, OPAMP-R4.2
unnamed: DISP-R9.2, DISP-R10.1, IC2.26 (PC3(ADC3)), TP3.TP
unnamed: AVR-C3.2, AVR-L1.1, IC2.18 (AVCC)
unnamed: DISP-R13.2, DISP-R14.1, IC2.28 (PC5(ADC5/SCL)), TP1.TP
unnamed: IC1.4 (V+), OPAMP-C1.1, OPAMP-L1.2
unnamed: DISP-R11.2, DISP-R12.1, IC2.27 (PC4(ADC4/SDA)), TP2.TP
unnamed: PWR-R4.1, U$1.4 (G)
unnamed: PWR-Q1.1 (G), PWR-Q2.3 (D), PWR-R2.1
unnamed: DISP-Q2.1 (G), DISP-R11.1
unnamed: DISP-Q1.1 (G), DISP-R9.1
unnamed: DISP-Q3.1 (G), DISP-R13.1
unnamed: IC1.6 (-IN), R25.2
unnamed: R28.1, TP12.TP
unnamed: S1.3, S1-E2.1, S1-R1.2
unnamed: S2.4 (P1), S2-R1.2, S2-R2.1
unnamed: LED2.C, LED2-R1.2
unnamed: LED1.C, LED1-R1.2
unnamed: IC1.7 (OUT), R24.2, R28.2
unnamed: IC1.3 (+IN), OPAMP-C3.1, OPAMP-R1.2, TP4.TP
unnamed: IC2.31 (PD1(TXD)), UART.2
unnamed: IC2.30 (PD0(RXD)), UART.1
unnamed: C10.1, IC1.5 (+IN), TP11.TP
unnamed: DIS1.6 (DP), DIS2.6 (DP), DIS3.6 (DP), DISP-R8\.1
unnamed: PWR-Q1.3 (D), PWR-R3.1, PWR-R4.2
unnamed: LED1.A, PWR-J1.5, PWR-J1.6, U$1.5 (D4), U$1.6 (D3), U$1.7 (D2), U$1.8 (D1)
unnamed: DIS1.2 (F), DIS2.2 (F), DIS3.2 (F), DISP-R6.1
unnamed: DIS1.1 (G), DIS2.1 (G), DIS3.1 (G), DISP-R7.1
unnamed: DIS1.4 (E), DIS2.4 (E), DIS3.4 (E), DISP-R5.1
unnamed: DIS1.5 (D), DIS2.5 (D), DIS3.5 (D), DISP-R4.1
unnamed: DIS1.7 (C), DIS2.7 (C), DIS3.7 (C), DISP-R3.1
unnamed: DIS1.9 (B), DIS2.9 (B), DIS3.9 (B), DISP-R2.1
unnamed: DIS1.10 (A), DIS2.10 (A), DIS3.10 (A), DISP-R1.1
PD5: IC2.9 (PD5(T1)), J4.1
PD6: IC2.10 (PD6(AIN0)), J4.2
PD7: IC2.11 (PD7(AIN1)), J4.3
RST: AVR-R1.2, IC2.29 (PC6(/RESET)), JP1.5
SCK: DISP-R1.2, IC2.17 (PB5(SCK)), JP1.3
SDFGHJK: IC1.1 (OUT), OPAMP-R2.2, OPAMP-R3.1
SENSOR0: OPAMP-R1.1, PWR-J1.2
THERMO0: IC2.23 (PC0(ADC0)), OPAMP-C2.1, OPAMP-R3.2
VCC: AVR-C1.1, AVR-L1.2, AVR-R1.1, IC2.4 (VCC), IC2.6 (VCC), IC3.2 (VOUT), J3.2, JP1.2, LDO-C2.2, LDO-C3.+, LED2.A, OPAMP-L1.1, S1-R1.1, S2-R1.1

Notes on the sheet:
two buttons
AVR n-Fets for the display
P-Fet to power the soldering iron
5V Power Supply
ISP Header
OpAmp for temp measurement (amp factor 431)
Display 3x 7 Segment
not used pads for another circuit at the lm324

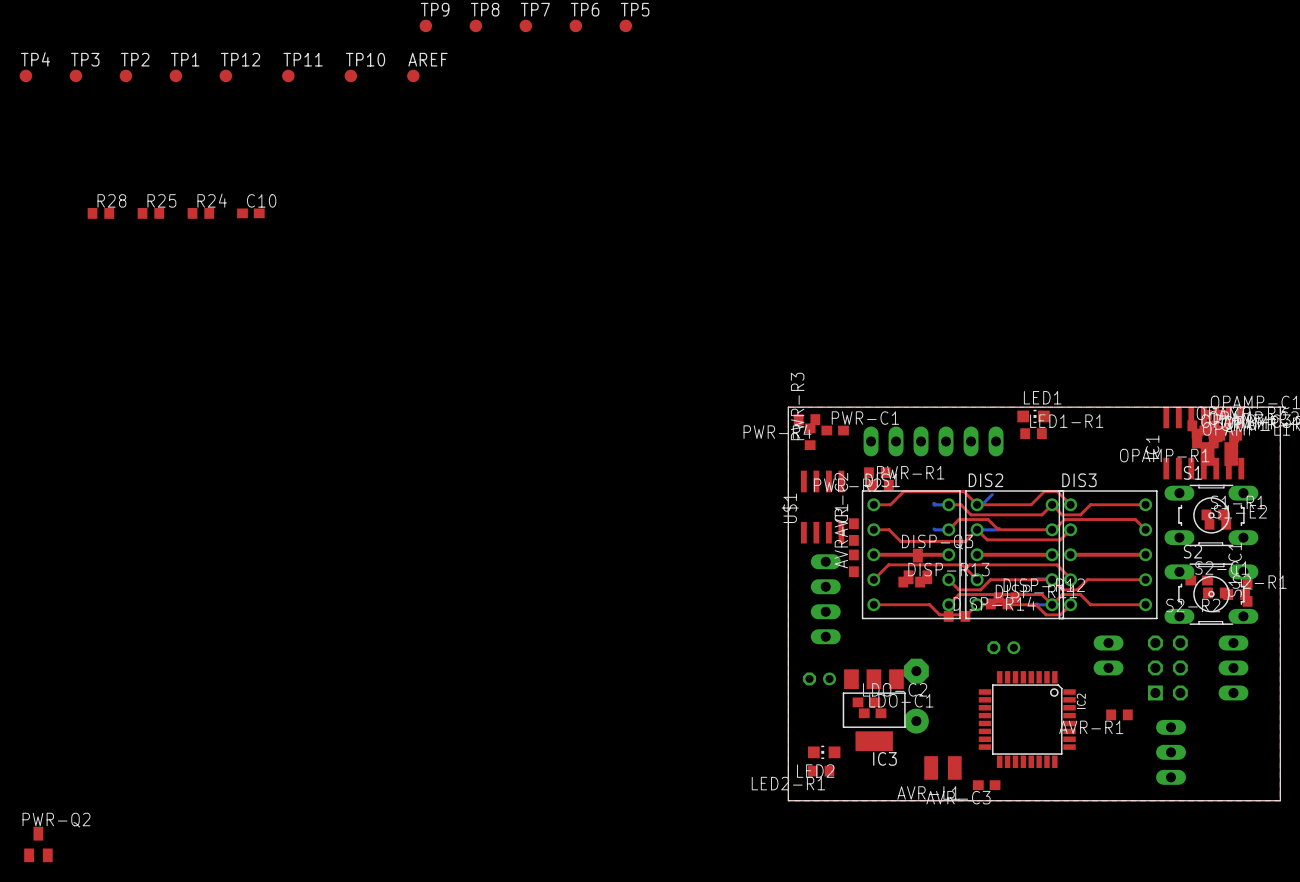
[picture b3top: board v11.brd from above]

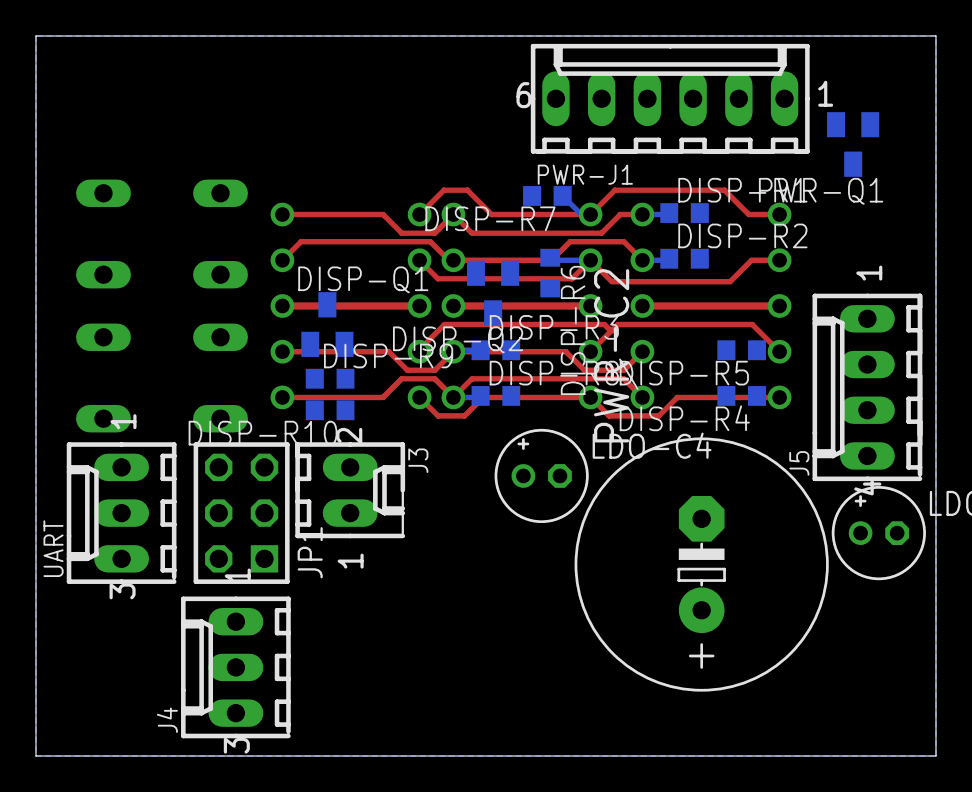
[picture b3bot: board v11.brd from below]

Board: 2 copper layers, 50.0 x 40.0 mm, 84 parts (22 on the bottom side), 60 nets.

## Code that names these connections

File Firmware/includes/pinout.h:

#pragma once

#include "../config.h"

#if (HW_VERSION == 1)
	#define LED_DDR   DDRC
	#define LED_PORT  PORTC
	#define LED0      (1<<PC3)
	#define LED1      (1<<PC4)
	#define LED2      (1<<PC5)

	#define DISP_DDR  DDRB
	#define DISP_PORT PORTB
	#define DISP_DOT  (1<<PB0)
	#define DISP_BR   (1<<PB1)
	#define DISP_BL   (1<<PB6)
	#define DISP_UR   (1<<PB3)
	#define DISP_UL   (1<<PB4)
	#define DISP_TOP  (1<<PB5)
	#define DISP_MID  (1<<PB2)
	#define DISP_BOT  (1<<PB7)
//	#define DISP_TOP  (1<<PB2)

	#define SENS0     PC0 // ADC0
	#define HALL      PC1 // ADC1

	#define PWR0_DDR  DDRD
	#define PWR0_PORT PORTD
	#define PWR0      PD4

//	#define BUTTON_UP (1<<PD2) // INT0
//	#define BUTTON_DN (1<<PD3) // INT1

// not used
//	#define J11       ADC7
//	#define J21       PD0 // RX
//	#define J22       PD1 // TX
//	#define J41       PD5
//	#define J42       PD6
//	#define J43       PD7

#elif (HW_VERSION == 12)
	#define LED_DDR   DDRD
	#define LED_PORT  PORTD
	#define LED0      (1<<PD7) // the lcd on the right
	#define LED1      (1<<PD6) // the lcd in the middle
	#define LED2      (1<<PD4) // the lcd on the left

	#define DISP_DDR  DDRB
	#define DISP_PORT PORTB
	#define DISP_DOT  (1<<PB4)
	#define DISP_BR   (1<<PB1)
	#define DISP_BL   (1<<PB7)
	#define DISP_UR   (1<<PB3)
	#define DISP_UL   (1<<PB0)
	#define DISP_TOP  (1<<PB2)
	#define DISP_MID  (1<<PB5)
	#define DISP_BOT  (1<<PB6)

	#define SENS0     PC0 // ADC0
	#define HALL      PC1 // ADC1

	#define PWR0_DDR  DDRD
	#define PWR0_PORT PORTD
	#define PWR0      PD5

	#ifdef ROTARY_ENCODER
		#define ROTARY_A_PIN     PINC
		#define ROTARY_B_PIN     PINC
		#define ROTARY_BUTTON_PIN		PINC
		
		#define ROTARY_A_PIN_NR     PC2
		#define ROTARY_B_PIN_NR     PC3
		#define ROTARY_BUTTON_PIN_NR	PC4
		
		#define ROTARY_A_PORT     PORTC
		#define ROTARY_B_PORT     PORTC
		#define ROTARY_BUTTON_PORT		PORTC
		
		#define ROTARY_A_DDR     DDRC
		#define ROTARY_B_DDR     DDRC
		#define ROTARY_BUTTON_DDR		DDRC
	#endif
	
//	#define BUTTON_UP (1<<PD2) // INT0
//	#define BUTTON_DN (1<<PD3) // INT1

// not used
//	#define J11       ADC7
//	#define J21       PD0 // RX
//	#define J22       PD1 // TX
//	#define J41       PD5
//	#define J42       PD6
//	#define J43       PD7
#endif
